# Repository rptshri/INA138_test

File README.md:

View this project on [CADLAB.io](https://cadlab.io/project/2197). 

# INA138_test

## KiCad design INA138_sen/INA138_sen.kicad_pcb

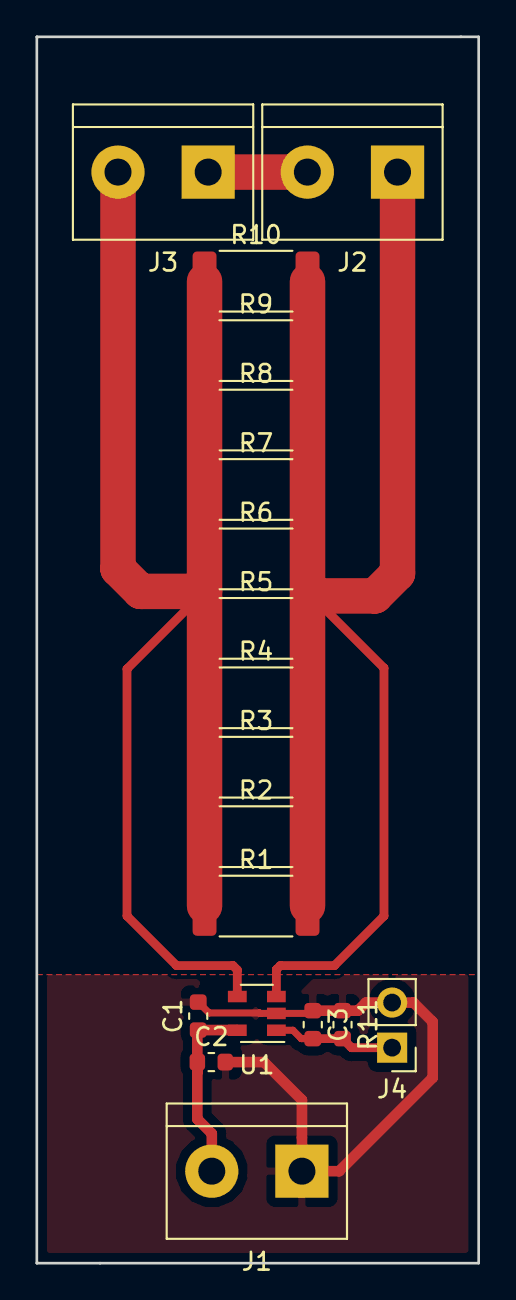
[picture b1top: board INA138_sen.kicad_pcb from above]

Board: 2 copper layers, 24.9 x 69.1 mm, 19 parts (0 on the bottom side), 6 nets.

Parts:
C1, C2, C3: C; C_0603_1608Metric
J1, J2, J3: Screw_Terminal_01x02; TerminalBlock_bornier-2_P5.08mm
J4: Conn_01x02_Female; PinHeader_1x02_P2.54mm_Vertical
R1, R2, R3, R4, R5, R6, R7, R8, R9, R10: R; R_2512_6332Metric
R11: R; R_0603_1608Metric
U1: INA138; SOT-23-5

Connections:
/I+: J2.1, R1.2, R2.2, R3.2, R4.2, R5.2, R6.2, R7.2, R8.2, R9.2, R10.2, U1.3
/I-: J3.2, R1.1, R2.1, R3.1, R4.1, R5.1, R6.1, R7.1, R8.1, R9.1, R10.1, U1.4
/VOUT: C3.2, J4.1, R11.2, U1.1
GND: C1.2, C2.2, C3.1, J1.1, J4.2, R11.1, U1.2
unnamed: J2.2, J3.1
VCC: C1.1, C2.1, J1.2, U1.5

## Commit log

2018-10-08 added schematic
2018-10-08 added PCB layout
2018-10-08 changed footprint of INA138
2018-10-08 Completed PCB layout
2019-10-12 Backlink to CADLAB.io has been added.
